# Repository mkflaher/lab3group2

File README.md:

# lab3group2

TTU ECE 333/4 - Project Lab 3 - Group 2

Sean Flaherty - Project Lead

Olivia Giles - System Designer

Dalton Scorgie - Software Programmer

Eric Garcia - Hardware Engineer

Working Robot Swarm:
https://streamable.com/tqe7s

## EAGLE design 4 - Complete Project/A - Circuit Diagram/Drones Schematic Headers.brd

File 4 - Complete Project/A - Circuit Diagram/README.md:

Complete circuit diagram, parts list and any schematic and/or circuit board layout files.

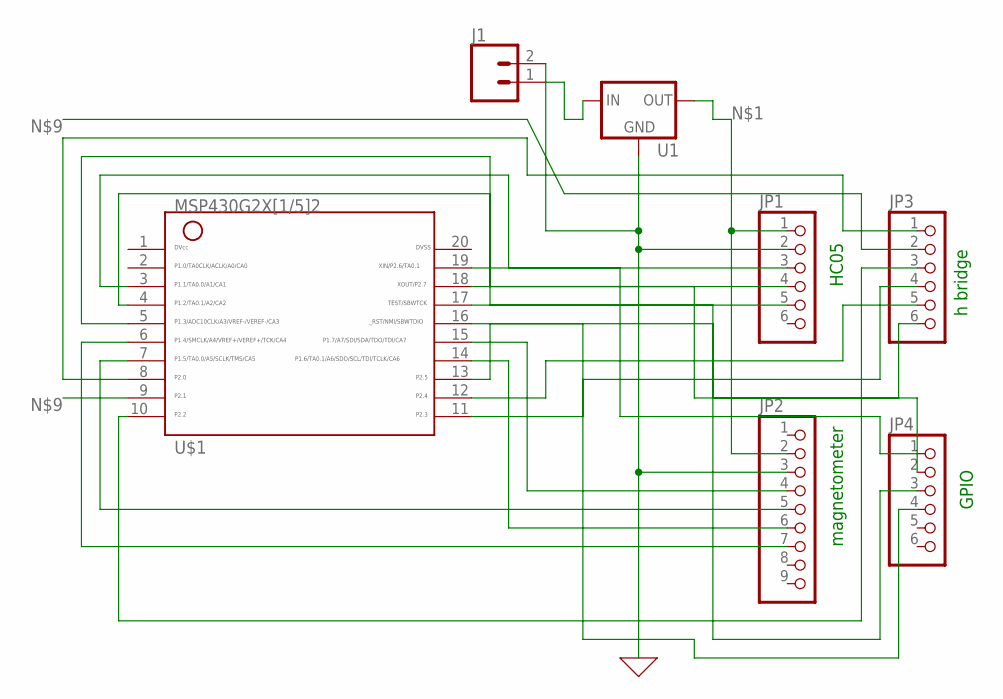
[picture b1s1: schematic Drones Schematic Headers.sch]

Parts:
J1: CONN_025MM; SCREWTERMINAL-5MM-2
JP1, JP3, JP4: PINHD-1X6; 1X06
JP2: PINHD-1X9; 1X09-BIG
U1: V_REG_78XXSINK; TO220-IGO
U$1: G2X[1/5]2---N20; N20

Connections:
GND: J1.2, JP1.2, JP2.3, U1.GND
unnamed: JP1.1, JP2.2, U1.OUT
unnamed: JP2.4, U$1.15
unnamed: JP2.5, U$1.7
unnamed: JP2.6, U$1.14
unnamed: JP2.7, U$1.6
unnamed: JP1.3, U$1.3
unnamed: JP1.4, U$1.4
unnamed: JP3.1, U$1.8
unnamed: JP3.2, U$1.9
unnamed: JP3.3, U$1.10
unnamed: JP3.4, U$1.11
unnamed: JP3.5, U$1.12
unnamed: JP3.6, U$1.13
unnamed: J1.1, U1.IN
unnamed: JP1.5, U$1.5
unnamed: JP4.1, U$1.19
unnamed: JP4.2, U$1.18
unnamed: JP4.3, U$1.17
unnamed: JP4.4, U$1.16

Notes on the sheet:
h bridge
GPIO
magnetometer
HC05

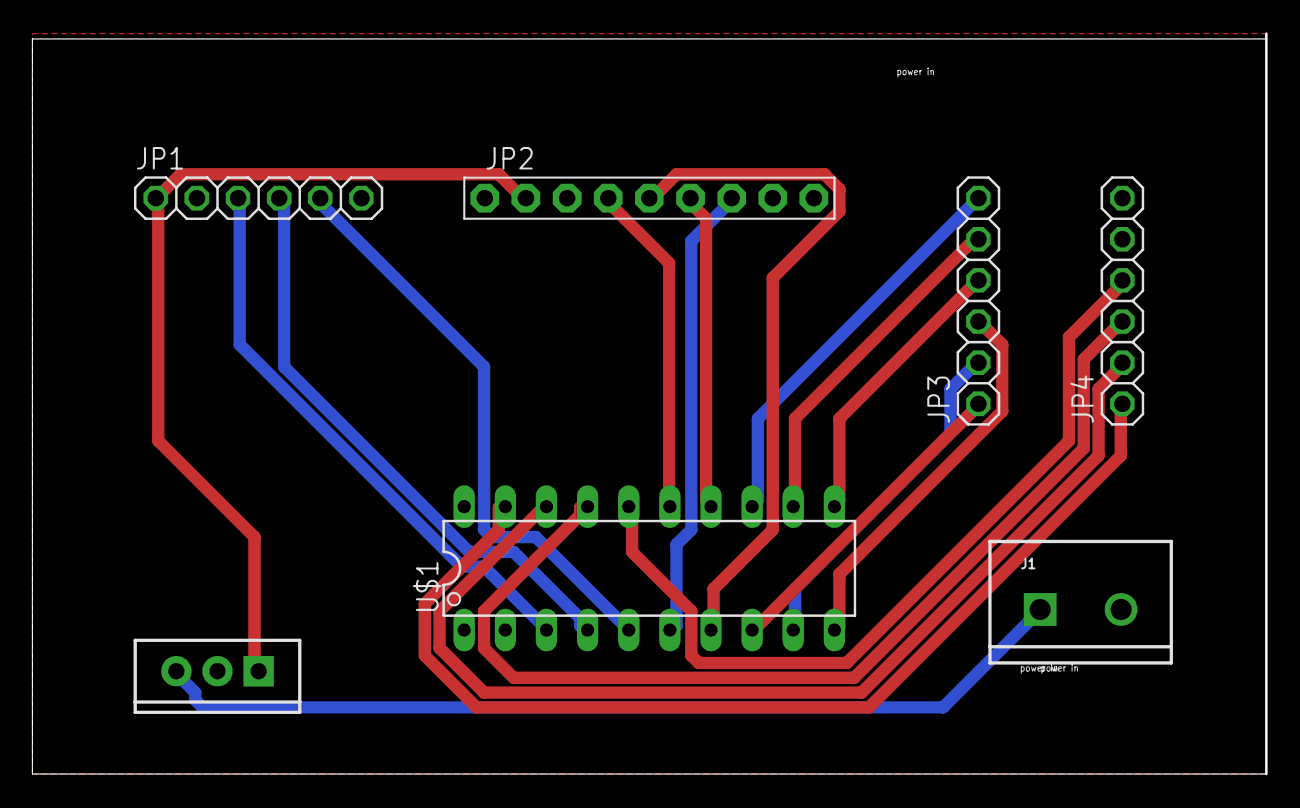
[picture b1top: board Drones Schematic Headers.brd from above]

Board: 2 copper layers, 76.2 x 45.7 mm, 7 parts (0 on the bottom side), 20 nets.

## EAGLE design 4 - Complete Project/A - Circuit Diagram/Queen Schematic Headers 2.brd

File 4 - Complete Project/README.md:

The fourth division must contain the following:
<ol>
  <li>
    complete circuit diagram, parts list and any schematic and/or circuit board layout files.
  </li>
  <li>
    complete flowchart, software listing and software files.
  </li>
  <li>
    timetable (Gantt Chart, original and actual, only)
  </li>
  <li>
    budget (Est. expense including labor & equip, original and actual, only)
  </li>
</ol>

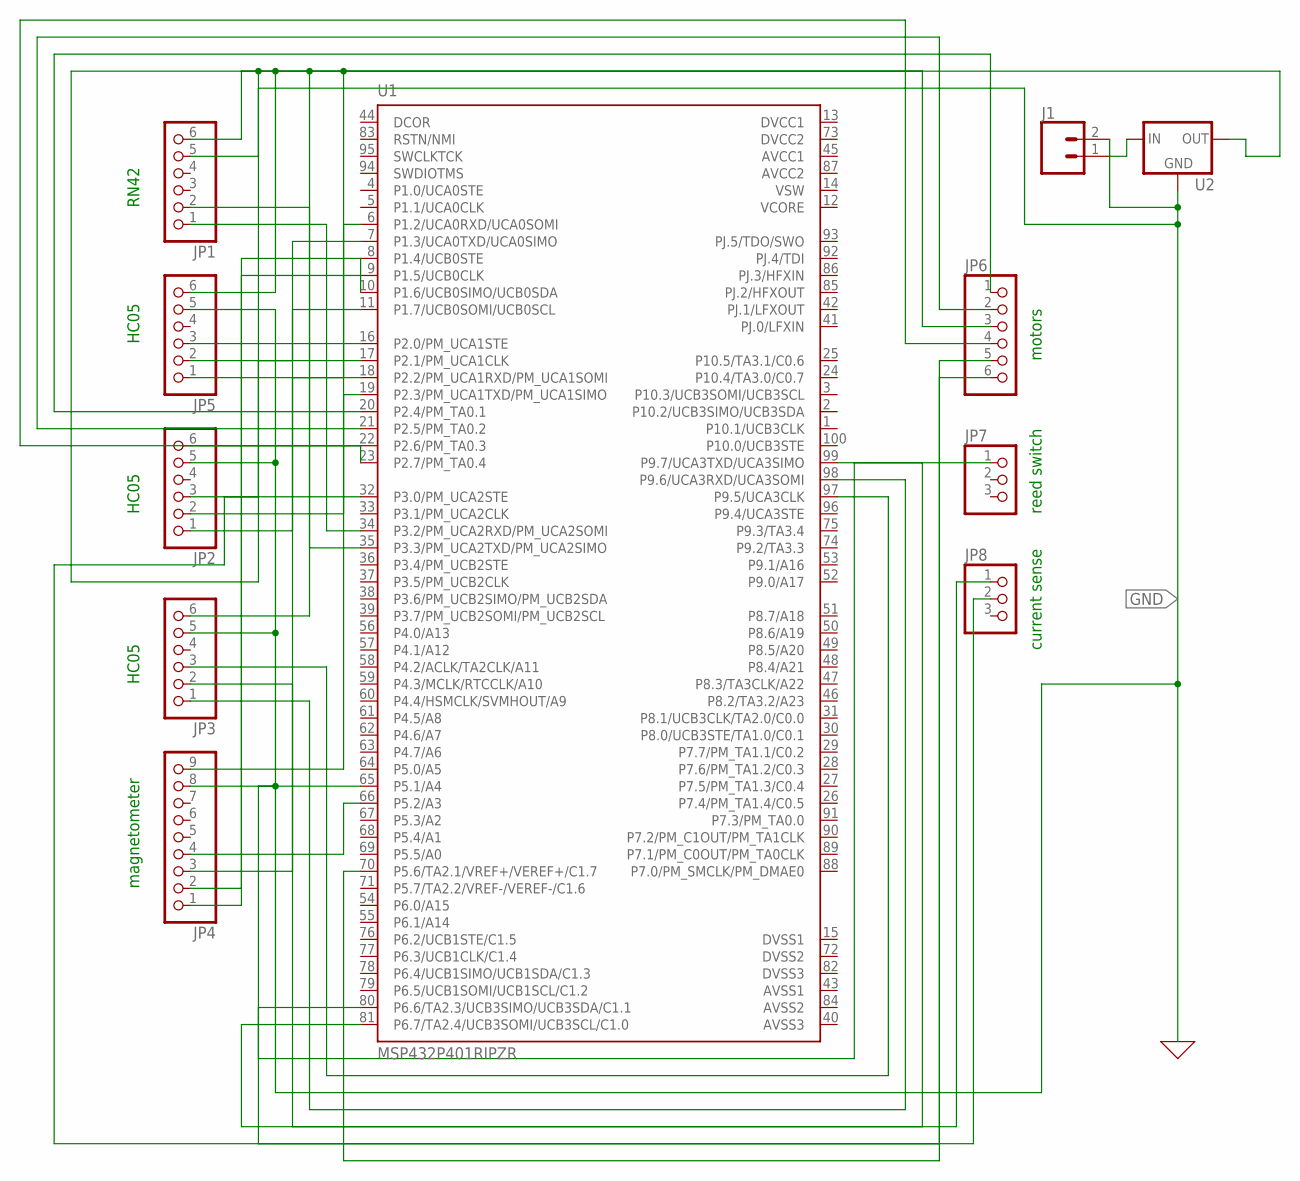
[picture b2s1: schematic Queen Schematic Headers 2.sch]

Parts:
J1: CONN_025MM; SCREWTERMINAL-5MM-2
JP1, JP2, JP3, JP5, JP6: PINHD-1X6; 1X06
JP4: PINHD-1X9; 1X09-BIG
JP7, JP8: PINHD-1X3; 1X03
U1: MSP432P401RIPZR; QFP50P1600X1600X160-100N
U2: V_REG_78XXSINK; TO220-IGO

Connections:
AVCC1: U1.45 (AVCC1)
AVCC2: U1.87 (AVCC2)
AVSS1: U1.43 (AVSS1)
AVSS2: U1.84 (AVSS2)
AVSS3: U1.40 (AVSS3)
DVCC1: U1.13 (DVCC1)
DVCC2: U1.73 (DVCC2)
DVSS1: U1.15 (DVSS1)
DVSS2: U1.72 (DVSS2)
DVSS3: U1.82 (DVSS3)
GND: J1.2, JP1.5, JP2.5, JP3.5, JP4.8, JP5.5, U2.GND
unnamed: JP1.6, JP2.6, JP3.6, JP4.9, JP5.6, U2.OUT
unnamed: JP1.1, U1.34 (P3.2/PM_UCA2RXD/PM_UCA2SOMI)
unnamed: JP1.2, U1.35 (P3.3/PM_UCA2TXD/PM_UCA2SIMO)
unnamed: JP3.2, U1.99 (P9.7/UCA3TXD/UCA3SIMO)
unnamed: JP5.1, U1.6 (P1.2/UCA0RXD/UCA0SOMI)
unnamed: JP5.2, U1.7 (P1.3/UCA0TXD/UCA0SIMO)
unnamed: JP5.3, U1.16 (P2.0/PM_UCA1STE)
unnamed: JP3.3, U1.97 (P9.5/UCA3CLK)
unnamed: JP2.1, U1.18 (P2.2/PM_UCA1RXD/PM_UCA1SOMI)
unnamed: JP2.2, U1.19 (P2.3/PM_UCA1TXD/PM_UCA1SIMO)
unnamed: JP2.3, U1.17 (P2.1/PM_UCA1CLK)
unnamed: JP4.1, U1.9 (P1.5/UCB0CLK)
unnamed: JP3.1, U1.98 (P9.6/UCA3RXD/UCA3SOMI)
unnamed: JP4.2, U1.10 (P1.6/UCB0SIMO/UCB0SDA)
unnamed: JP4.3, U1.11 (P1.7/UCB0SOMI/UCB0SCL)
unnamed: JP4.4, U1.66 (P5.2/A3)
unnamed: JP6.1, U1.20 (P2.4/PM_TA0.1)
unnamed: J1.1, U2.IN
unnamed: JP6.2, U1.21 (P2.5/PM_TA0.2)
unnamed: JP6.3, U1.22 (P2.6/PM_TA0.3)
unnamed: JP6.4, U1.23 (P2.7/PM_TA0.4)
unnamed: JP6.5, U1.32 (P3.0/PM_UCA2STE)
unnamed: JP6.6, U1.70 (P5.6/TA2.1/VREF+/VEREF+/C1.7)
unnamed: JP7.1, U1.80 (P6.6/TA2.3/UCB3SIMO/UCB3SDA/C1.1)
unnamed: JP8.1, U1.81 (P6.7/TA2.4/UCB3SOMI/UCB3SCL/C1.0)
unnamed: JP8.2, U1.65 (P5.1/A4)
VCORE: U1.12 (VCORE)
VSW: U1.14 (VSW)

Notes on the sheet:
RN42
HC05
magnetometer
motors
reed switch
current sense

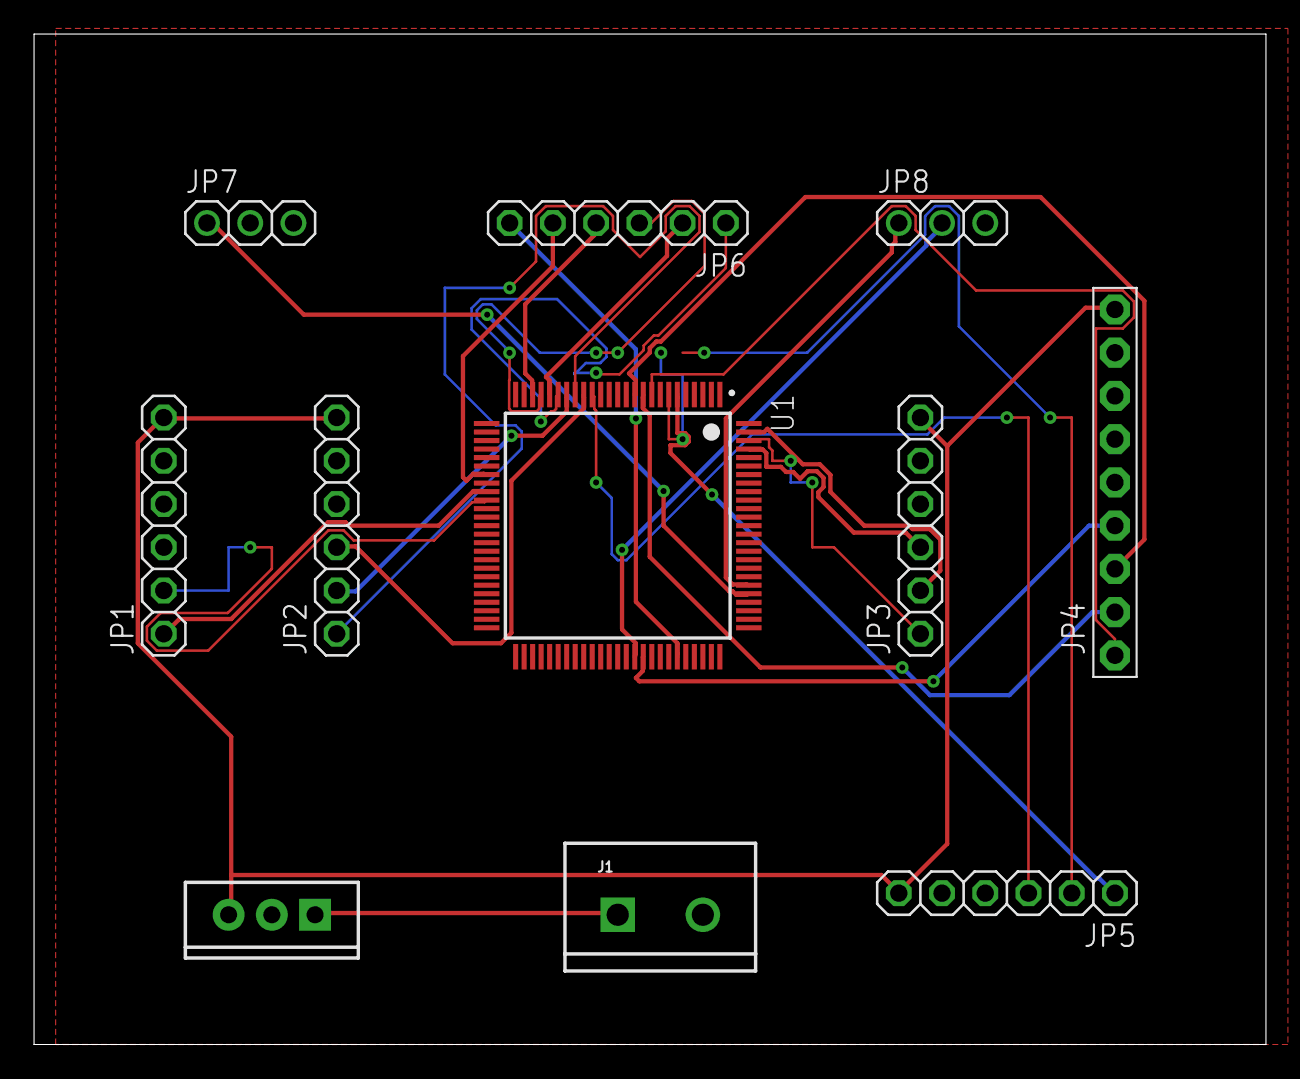
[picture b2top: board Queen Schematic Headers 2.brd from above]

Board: 2 copper layers, 72.4 x 59.4 mm, 11 parts (0 on the bottom side), 27 nets.

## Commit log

2018-02-05 Added BasicBlockDiagram.png
2018-02-06 Added flagship.png
2018-02-06 Added drone.png
2018-02-07 Added block.png
2018-02-07 Changed block.png
2018-02-07 Added magnetometer to block.png
2018-02-07 Made flagship.png transparent
2018-02-07 Fixed mistake on flagship
2018-02-07 Fixed flagship again
2018-02-07 Made drone transparent
2018-02-08 Added magnetometer to msp432 (block.png)
2018-02-13 trilateration image
2018-02-13 added algorithm for trilateration
2018-02-14 Changed Bluetooth connections
2018-02-16 bluetooth debug console
2018-02-20 added gui
2018-02-21 map drawing added to gui
2018-02-28 obstacles in gui
2018-03-01 Added MoreDetailedBlock.png
2018-03-01 Fixed size on more detailed block
2018-03-07 pathfinding added to gui
2018-03-08 Create Drone-MSP430
2018-03-08 Create folder for Drone and Reed Me
2018-03-08 Rename Read-Me.txt to README.md
2018-03-08 Update README to include pin connections
2018-03-09 Create MSP432 UART wout Test or Mag
2018-03-19 Create B - Software
2018-03-19 Moved file
2018-03-19 Rename gui/room1.csv to 4 - Complete Project/B - Software/GUI/room1.csv
2018-03-19 Rename gui/gui.py to 4 - Complete Project/B - Software/GUI/gui.py
2018-03-19 Rename Drone/main.c to 4 - Complete Project/B - Software/Drone/main.c
2018-03-19 Rename Drone/README.md to 4 - Complete Project/B - Software/Drone/README.md
2018-03-19 Rename bdebug/btmon.py to 4- Complete Project/B - Software/bdebug/btmon.py
2018-03-19 Rename bdebug/bdebug.py to 4- Complete Project/B - Software/bdebug/bdebug.py
2018-03-19 Rename 4- Complete Project/B - Software/bdebug/bdebug.py to 4 - Complete Project/B - Software/bdebug/bdebug.py
2018-03-19 Rename 4- Complete Project/B - Software/bdebug/btmon.py to 4 - Complete Project/B - Software/bdebug/btmon.py
2018-03-19 Create Notes on magnetometer and SPI
2018-03-21 commit before merge
2018-03-21 added trilateration algorithm to notes
2018-03-22 added datasheets
2018-03-22 datasheets
2018-03-28 added direction string
2018-04-04 Create MSP432 UART send and receive
2018-04-09 Added Reed Switch.png
2018-04-11 Greenboard
    PCB files
2018-04-11 Greenboard
    PCB designs
2018-04-13 Motor direction and PWM controlled via Bluetooth
2018-04-18 Commands for faster and slower
2018-04-25 Notes on driving the Drone
2018-05-04 Add files via upload
    Assembled robots on display
2018-05-08 MSP432 Final
    Final code for queen bot. Has communication via UART and drive commands
2018-05-08 base STL
2018-05-11 final commit

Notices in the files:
parts and their libraries:
SparkFun-Connectors: Licensing: Creative Commons ShareAlike 4.0 International - https://creativecommons.org/licenses/by-sa/4.0
